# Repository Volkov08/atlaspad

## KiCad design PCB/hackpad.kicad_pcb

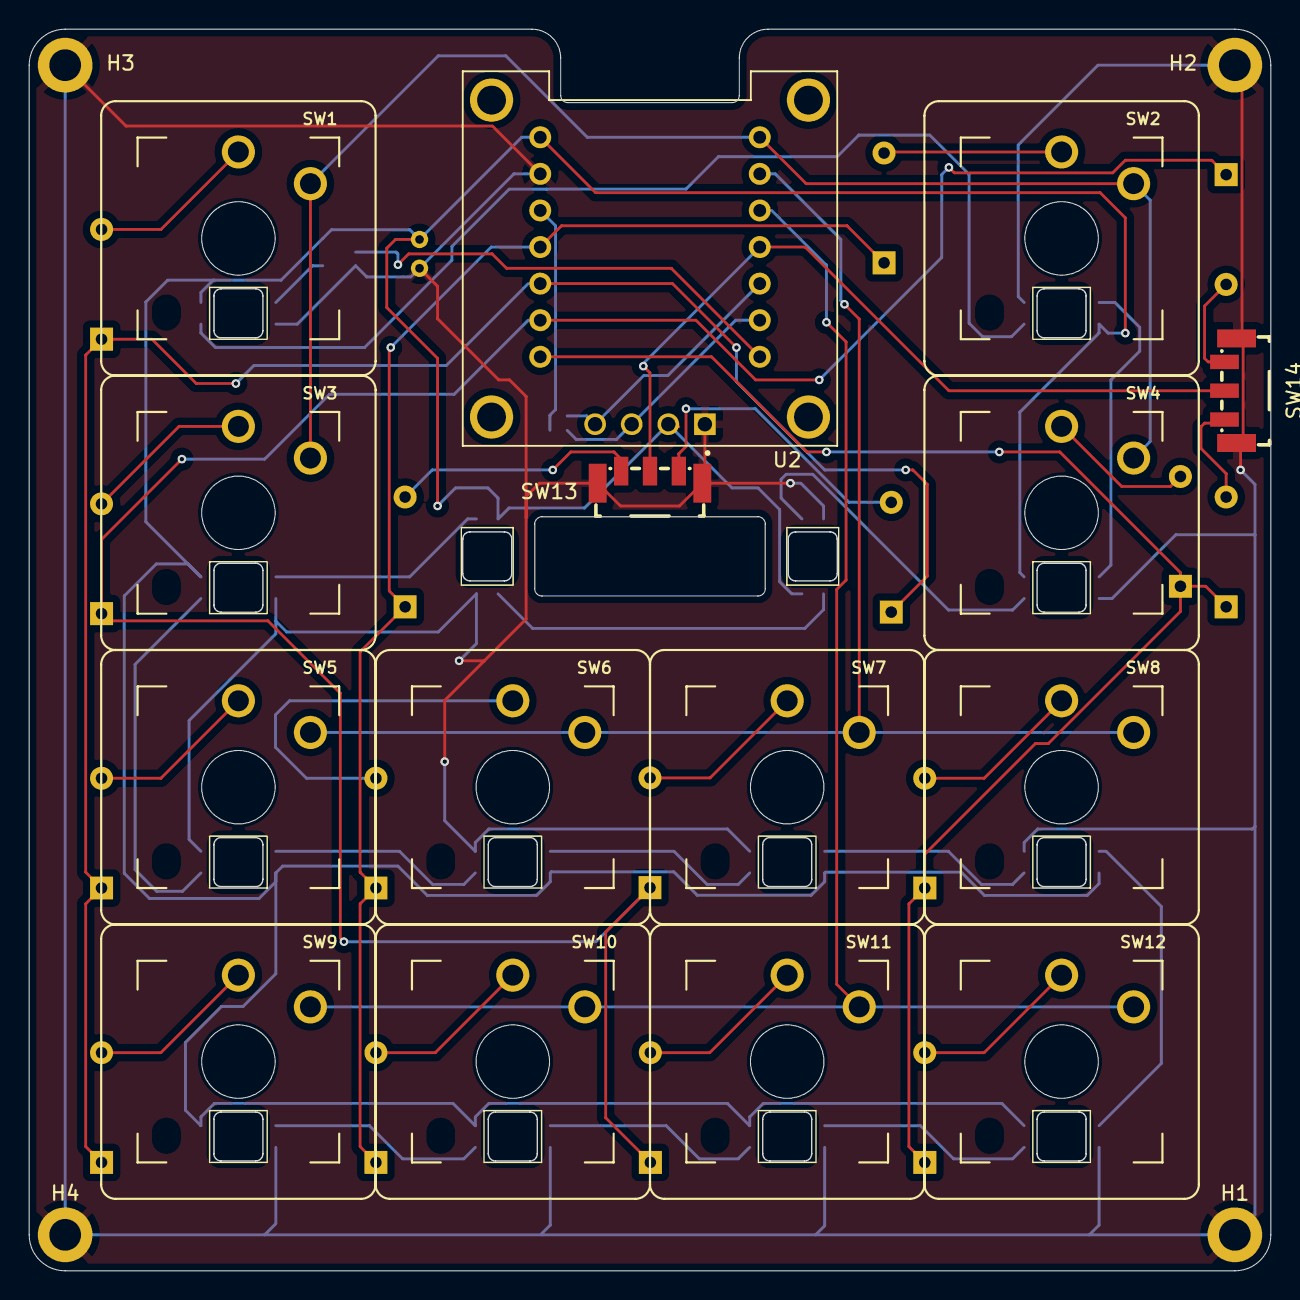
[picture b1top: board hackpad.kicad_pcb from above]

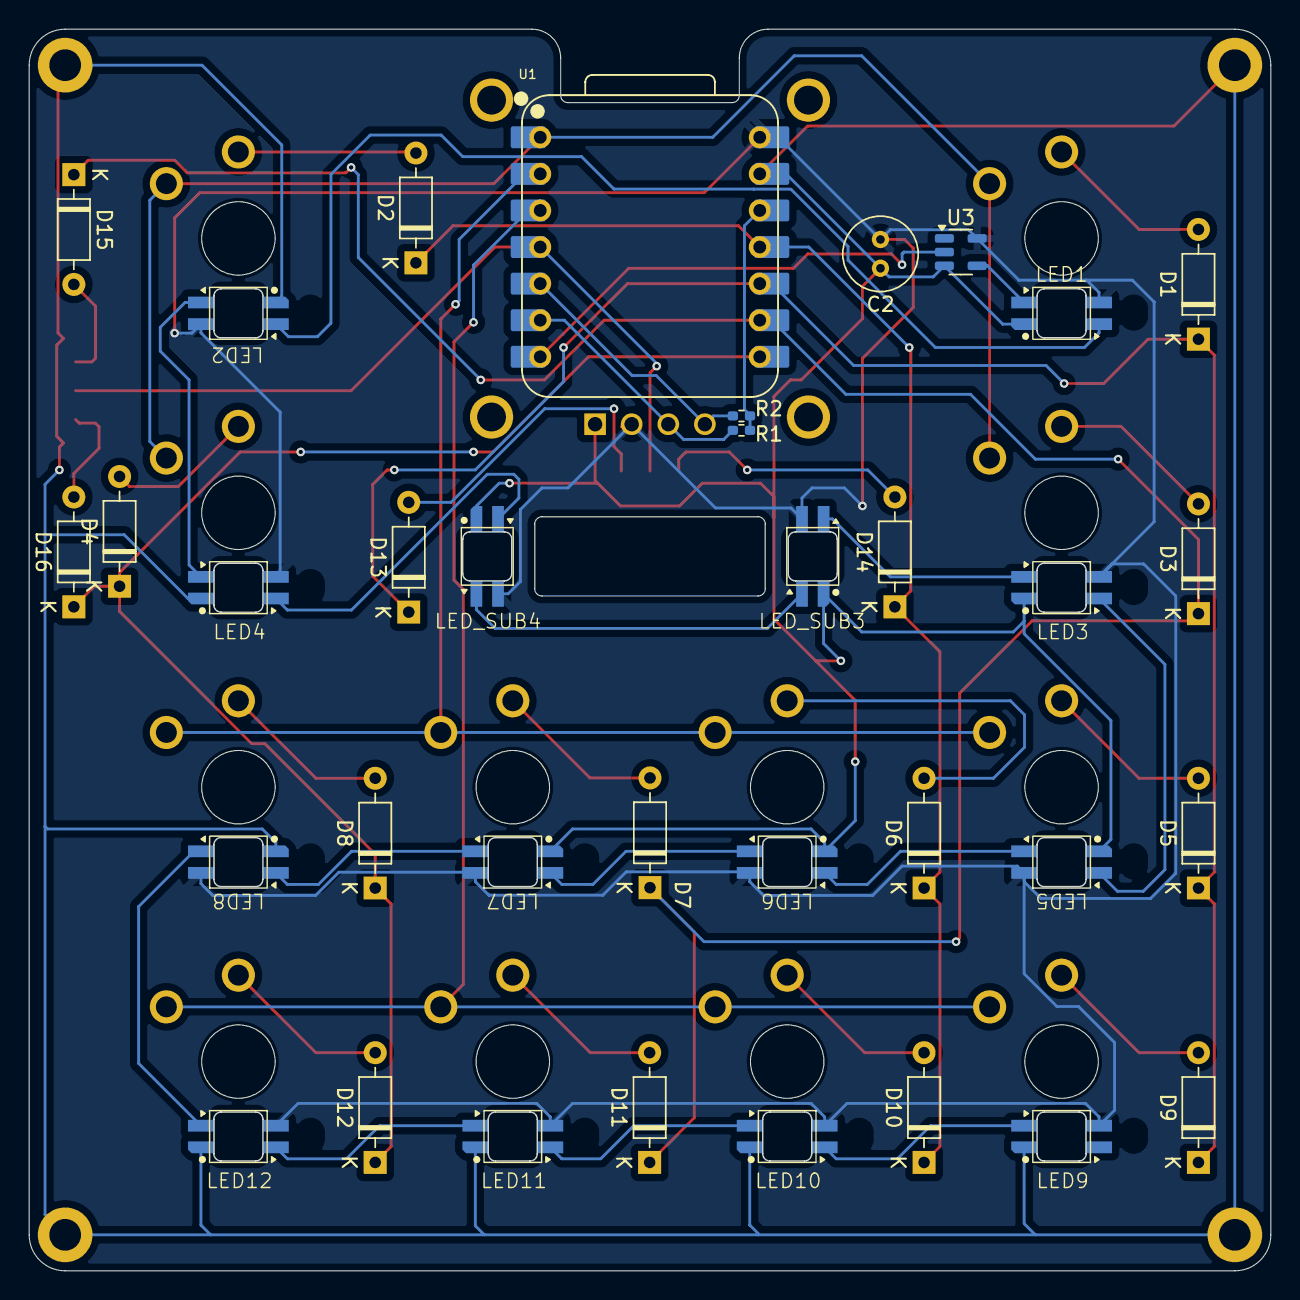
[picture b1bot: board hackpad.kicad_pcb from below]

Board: 2 copper layers, 86.2 x 86.2 mm, 54 parts (21 on the bottom side), 44 nets.

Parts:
C2: 22uF; C_Radial_D5.0mm_H7.0mm_P2.00mm
D1, D2, D3, D4, D5, D6, D7, D8, D9, D10, D11, D12, D13, D14, D15, D16: 1N4148; D_DO-35_SOD27_P7.62mm_Horizontal
H1, H2, H3, H4: MountingHole_Pad; MountingHole_2.2mm_M2_DIN965_Pad
LED1, LED2, LED3, LED4, LED5, LED6, LED7, LED8, LED9, LED10, LED11, LED12: SK6812MINIE; SK6812MINI-E-Reverse
LED_SUB3, LED_SUB4: SK6812MINIE; SK6812MINI-E-Reverse
R1, R2: 10k; R_0402_1005Metric_Pad0.72x0.64mm_HandSolder
SW1, SW2, SW3, SW4, SW5, SW6, SW7, SW8, SW9, SW10, SW11, SW12: Keyswitch; Kailh-PG1353-Solderable-1U
SW13, SW14: EC05E1220203; SW-SMD_EC05E1220203
U1: XIAO-RP2040-DIP
U2: DM-OLED096-636; MODULE_DM-OLED096-636
U3: SN74LV1T34DBV; SOT-23-5

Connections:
3V3: R1.1, R2.1, U1.12 (3V3)
COL0: SW1.1, SW2.1, SW3.1, SW4.1, U1.1 (GPIO26/ADC0/A0)
COL1: SW5.1, SW6.1, SW7.1, SW8.1, U1.2 (GPIO27/ADC1/A1)
COL2: SW9.1, SW10.1, SW11.1, SW12.1, U1.3 (GPIO28/ADC2/A2)
COL3: SW13.C, SW14.C, U1.4 (GPIO29/ADC3/A3)
GND: C2.1, H1.1, H2.1, H3.1, H4.1, LED1.3 (GND), LED2.3 (GND), LED3.3 (GND), LED4.3 (GND), LED5.3 (GND), LED6.3 (GND), LED7.3 (GND), LED8.3 (GND), LED9.3 (GND), LED10.3 (GND), LED11.3 (GND), LED12.3 (GND), LED_SUB3.3 (GND), LED_SUB4.3 (GND), SW13.4, SW13.5, SW14.4, SW14.5, U1.13 (GND), U2.1 (GND), U3.3 (GND)
LED_DIN: U1.7 (GPIO0/TX), U3.2 (A)
LED_DIN_Shifted: LED1.4 (DIN), U3.4 (Y)
unnamed: D1.2 (A), SW1.2
unnamed: D2.2 (A), SW2.2
unnamed: D3.2 (A), SW3.2
unnamed: D4.2 (A), SW4.2
unnamed: D5.2 (A), SW5.2
unnamed: D6.2 (A), SW6.2
unnamed: D7.2 (A), SW7.2
unnamed: D8.2 (A), SW8.2
unnamed: D9.2 (A), SW9.2
unnamed: D10.2 (A), SW10.2
unnamed: D11.2 (A), SW11.2
unnamed: D12.2 (A), SW12.2
unnamed: D13.2 (A), SW13.B
unnamed: D14.2 (A), SW13.A
unnamed: D15.2 (A), SW14.B
unnamed: D16.2 (A), SW14.A
unnamed: LED1.2 (DOUT), LED2.4 (DIN)
unnamed: LED2.2 (DOUT), LED4.4 (DIN)
unnamed: LED3.4 (DIN), LED_SUB3.2 (DOUT)
unnamed: LED3.2 (DOUT), LED5.4 (DIN)
unnamed: LED4.2 (DOUT), LED_SUB4.4 (DIN)
unnamed: LED5.2 (DOUT), LED6.4 (DIN)
unnamed: LED6.2 (DOUT), LED7.4 (DIN)
unnamed: LED7.2 (DOUT), LED8.4 (DIN)
unnamed: LED10.4 (DIN), LED11.2 (DOUT)
unnamed: LED9.4 (DIN), LED10.2 (DOUT)
unnamed: LED11.4 (DIN), LED12.2 (DOUT)
unnamed: LED8.2 (DOUT), LED12.4 (DIN)
unnamed: LED_SUB3.4 (DIN), LED_SUB4.2 (DOUT)
ROW0: D1.1 (K), D5.1 (K), D9.1 (K), D13.1 (K), U1.10 (GPIO4/MISO)
ROW1: D2.1 (K), D6.1 (K), D10.1 (K), D14.1 (K), U1.11 (GPIO3/MOSI)
ROW2: D3.1 (K), D7.1 (K), D11.1 (K), D15.1 (K), U1.9 (GPIO2/SCK)
ROW3: D4.1 (K), D8.1 (K), D12.1 (K), D16.1 (K), U1.8 (GPIO1/RX)
SCL: R1.2, U1.6 (GPIO7/SCL), U2.3 (SCL)
SDA: R2.2, U1.5 (GPIO6/SDA), U2.4 (SDA)
VCC: C2.2, LED1.1 (VCC), LED2.1 (VCC), LED3.1 (VCC), LED4.1 (VCC), LED5.1 (VCC), LED6.1 (VCC), LED7.1 (VCC), LED8.1 (VCC), LED9.1 (VCC), LED10.1 (VCC), LED11.1 (VCC), LED12.1 (VCC), LED_SUB3.1 (VCC), LED_SUB4.1 (VCC), U1.14 (VBUS), U2.2 (VCC_IN), U3.5 (VCC)

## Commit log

2025-02-15 did pcb
2025-02-15 did gitignore properly
2025-02-15 made 3d models of pcb
2025-02-19 case done
2025-02-20 QMK works finally holy shit
2025-02-20 finished for submission
2025-02-21 branding uhhh
